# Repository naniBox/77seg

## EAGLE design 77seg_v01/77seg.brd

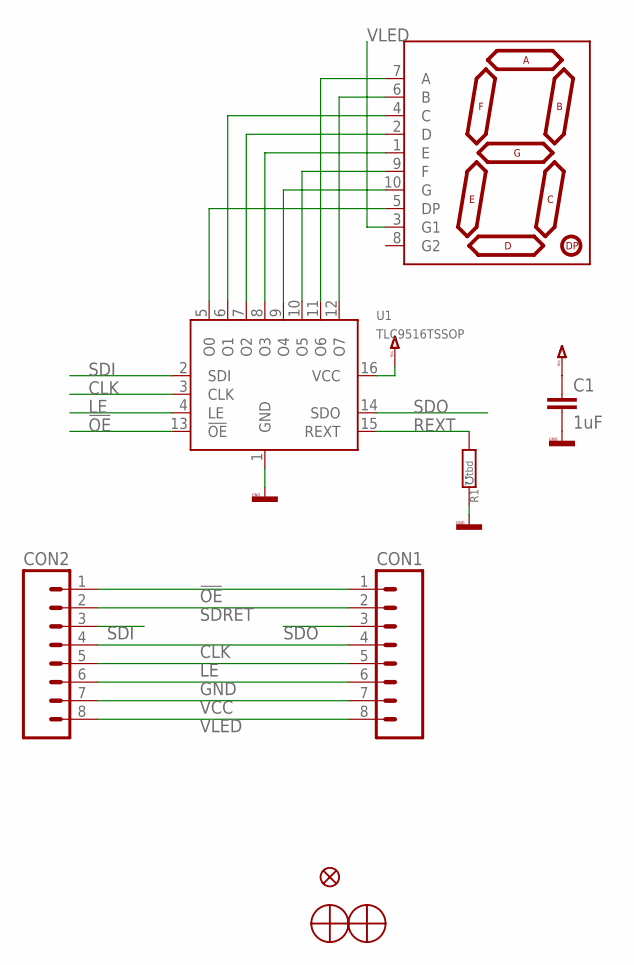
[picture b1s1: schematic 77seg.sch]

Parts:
C1: 1uF; C0603
CON1, CON2: M081.27MM_NO1; 1X08_1.27MM_NO1
JP1: FIDUCIAL1X1.5; FIDUCIAL_1X1.5
R1: tbd; R0603
U1: TLC9516TSSOP; TSSOP16
U$1: 7-SEGMENT-DISPLAYPTH; 7-SEGMENT-DISPLAY
U$2, U$3: SCREW_NOGND; SCREW_M2_NOVIAS

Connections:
!OE: CON1.1, CON2.1, U1.13 (!OE)
CLK: CON1.4, CON2.4, U1.3 (CLK)
GND: C1.2, CON1.6, CON2.6, R1.2, U1.1 (GND)
LE: CON1.5, CON2.5, U1.4 (LE)
unnamed: U1.10 (O5), U$1.9 (F)
unnamed: U1.9 (O4), U$1.10 (G)
unnamed: U1.11 (O6), U$1.7 (A)
unnamed: U1.12 (O7), U$1.6 (B)
unnamed: U1.6 (O1), U$1.4 (C)
unnamed: U1.7 (O2), U$1.2 (D)
unnamed: U1.8 (O3), U$1.1 (E)
unnamed: U1.5 (O0), U$1.5 (DP)
REXT: R1.1, U1.15 (REXT)
SDI: CON2.3, U1.2 (SDI)
SDO: CON1.3, U1.14 (SDO)
SDRET: CON1.2, CON2.2
VCC: C1.1, CON1.7, CON2.7, U1.16 (VCC)
VLED: CON1.8, CON2.8, U$1.3 (G1)

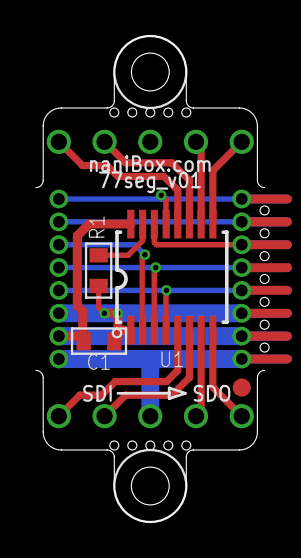
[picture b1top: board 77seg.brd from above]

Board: 2 copper layers, 12.7 x 27.0 mm, 9 parts (1 on the bottom side), 18 nets.

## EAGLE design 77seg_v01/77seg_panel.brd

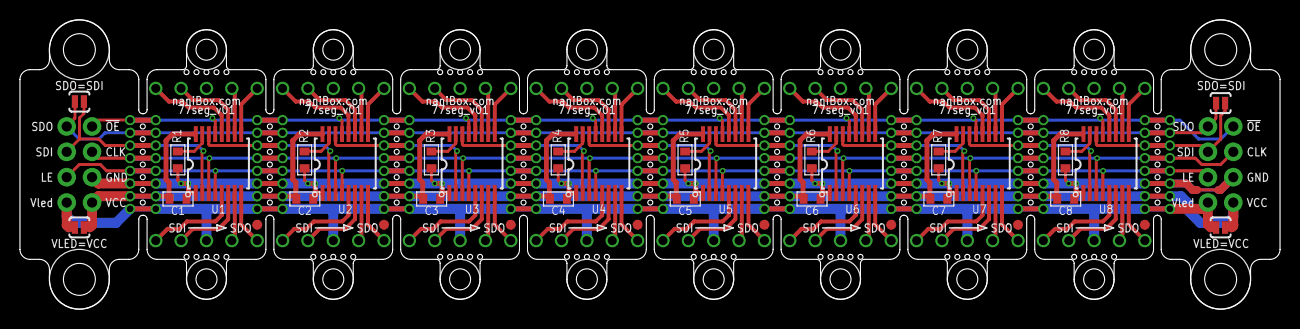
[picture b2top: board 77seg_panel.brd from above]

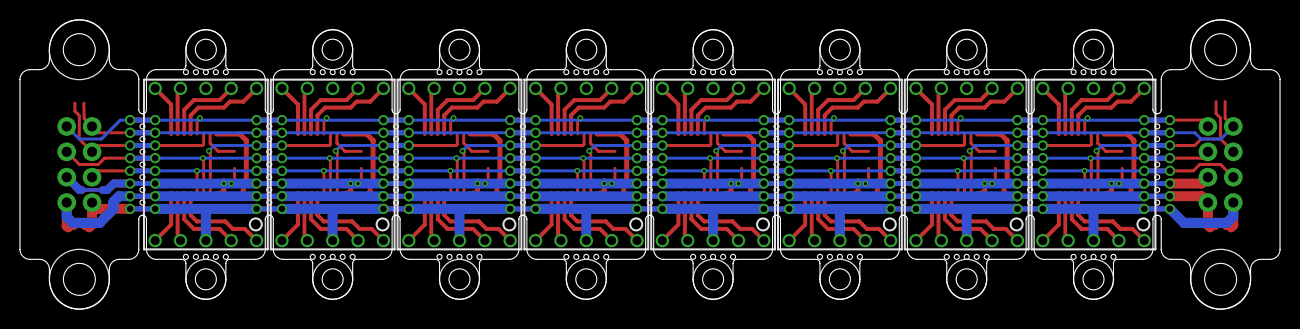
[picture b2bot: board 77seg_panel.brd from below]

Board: 2 copper layers, 126.2 x 29.0 mm, 86 parts (8 on the bottom side), 152 nets.

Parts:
C1, C2, C3, C4, C5, C6, C7, C8: 1uF; C0603
CON1, CON2, CON7, CON8, CON9, CON10, CON11, CON12, CON13, CON14, CON15, CON16, CON17, CON18, CON19, CON20, CON21, CON22: 1X08_1.27MM_NO1
CON3, CON4, CON5, CON6: M04NO1; 1X04_NO1
JP1, JP2, JP3, JP4, JP5, JP6, JP7, JP8: FIDUCIAL1X1.5; FIDUCIAL_1X1.5
R1, R2, R3, R4, R5, R6, R7, R8: tbd; R0603
SDI=SDO1: SJ_2S-NO
SDO=SDI: SJ_2S-NO
U1, U2, U3, U4, U5, U6, U7, U8: TLC9516TSSOP; TSSOP16
U$1, U$2, U$3, U$4: SCREW_NOGNDM3_REDUCED; SCREW_M3_REDUCED
U$5, U$8, U$11, U$14, U$17, U$20, U$23, U$26: 7-SEGMENT-DISPLAYPTH; 7-SEGMENT-DISPLAY
U$6, U$7, U$9, U$10, U$12, U$13, U$15, U$16, U$18, U$19, U$21, U$22, U$24, U$25, U$27, U$28: SCREW_NOGND; SCREW_M2_NOVIAS
VLED=VCC, VLED=VCC1: SJ_2S-NO

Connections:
!OE: CON1.1, CON2.1, CON3.1, CON5.1
!OE1: CON7.1, CON8.1, U1.13
!OE2: CON9.1, CON10.1, U2.13
!OE3: CON11.1, CON12.1, U3.13
!OE4: CON13.1, CON14.1, U4.13
!OE5: CON15.1, CON16.1, U5.13
!OE6: CON17.1, CON18.1, U6.13
!OE7: CON19.1, CON20.1, U7.13
!OE8: CON21.1, CON22.1, U8.13
CLK: CON1.4, CON2.4, CON3.2, CON5.2
CLK1: CON7.4, CON8.4, U1.3
CLK2: CON9.4, CON10.4, U2.3
CLK3: CON11.4, CON12.4, U3.3
CLK4: CON13.4, CON14.4, U4.3
CLK5: CON15.4, CON16.4, U5.3
CLK6: CON17.4, CON18.4, U6.3
CLK7: CON19.4, CON20.4, U7.3
CLK8: CON21.4, CON22.4, U8.3
GND: CON1.6, CON2.6, CON3.3, CON5.3
GND1: C1.2, CON7.6, CON8.6, R1.2, U1.1
GND2: C2.2, CON9.6, CON10.6, R2.2, U2.1
GND3: C3.2, CON11.6, CON12.6, R3.2, U3.1
GND4: C4.2, CON13.6, CON14.6, R4.2, U4.1
GND5: C5.2, CON15.6, CON16.6, R5.2, U5.1
GND6: C6.2, CON17.6, CON18.6, R6.2, U6.1
GND7: C7.2, CON19.6, CON20.6, R7.2, U7.1
GND8: C8.2, CON21.6, CON22.6, R8.2, U8.1
LE: CON1.5, CON2.5, CON4.3, CON6.3
LE1: CON7.5, CON8.5, U1.4
LE2: CON9.5, CON10.5, U2.4
LE3: CON11.5, CON12.5, U3.4
LE4: CON13.5, CON14.5, U4.4
LE5: CON15.5, CON16.5, U5.4
LE6: CON17.5, CON18.5, U6.4
LE7: CON19.5, CON20.5, U7.4
LE8: CON21.5, CON22.5, U8.4
unnamed: U2.10, U$8.9
unnamed: U2.9, U$8.10
unnamed: U1.10, U$5.9
unnamed: U1.9, U$5.10
unnamed: U2.11, U$8.7
unnamed: U2.12, U$8.6
unnamed: U2.6, U$8.4
unnamed: U2.7, U$8.2
unnamed: U2.8, U$8.1
unnamed: U1.11, U$5.7
unnamed: U1.12, U$5.6
unnamed: U1.6, U$5.4
unnamed: U1.7, U$5.2
unnamed: U1.8, U$5.1
unnamed: U2.5, U$8.5
unnamed: U3.10, U$11.9
unnamed: U1.5, U$5.5
unnamed: U3.9, U$11.10
unnamed: U3.11, U$11.7
unnamed: U3.12, U$11.6
unnamed: U3.6, U$11.4
unnamed: U3.7, U$11.2
unnamed: U3.8, U$11.1
unnamed: U3.5, U$11.5
unnamed: U4.10, U$14.9
unnamed: U4.9, U$14.10
unnamed: U4.11, U$14.7
unnamed: U4.12, U$14.6
unnamed: U4.6, U$14.4
unnamed: U4.7, U$14.2
unnamed: U4.8, U$14.1
unnamed: U4.5, U$14.5
unnamed: U5.10, U$17.9
unnamed: U5.9, U$17.10
unnamed: U5.11, U$17.7
unnamed: U5.12, U$17.6
unnamed: U5.6, U$17.4
unnamed: U5.7, U$17.2
unnamed: U5.8, U$17.1
unnamed: U5.5, U$17.5
unnamed: U6.10, U$20.9
unnamed: U6.9, U$20.10
unnamed: U6.11, U$20.7
unnamed: U6.12, U$20.6
unnamed: U6.6, U$20.4
unnamed: U6.7, U$20.2
unnamed: U6.8, U$20.1
unnamed: U6.5, U$20.5
unnamed: U7.10, U$23.9
unnamed: U7.9, U$23.10
unnamed: U7.11, U$23.7
unnamed: U7.12, U$23.6
unnamed: U7.6, U$23.4
unnamed: U7.7, U$23.2
unnamed: U7.8, U$23.1
unnamed: U7.5, U$23.5
unnamed: U8.10, U$26.9
unnamed: U8.9, U$26.10
unnamed: U8.11, U$26.7
unnamed: U8.12, U$26.6
unnamed: U8.6, U$26.4
unnamed: U8.7, U$26.2
unnamed: U8.8, U$26.1
unnamed: U8.5, U$26.5
REXT: R1.1, U1.15
REXT1: R2.1, U2.15
REXT2: R3.1, U3.15
REXT3: R4.1, U4.15
REXT4: R5.1, U5.15
REXT5: R6.1, U6.15
REXT6: R7.1, U7.15
REXT7: R8.1, U8.15
SDI: CON1.3, CON2.3, CON4.2, CON6.2, SDI=SDO1.1, SDO=SDI.1
SDI1: CON8.3, U1.2
SDI2: CON10.3, U2.2
SDI3: CON12.3, U3.2
SDI4: CON14.3, U4.2
SDI5: CON16.3, U5.2
SDI6: CON18.3, U6.2
SDI7: CON20.3, U7.2
SDI8: CON22.3, U8.2
SDO: CON1.2, CON2.2, CON4.1, CON6.1, SDI=SDO1.2, SDO=SDI.2
SDO1: CON7.3, U1.14
SDO2: CON9.3, U2.14
SDO3: CON11.3, U3.14
SDO4: CON13.3, U4.14
SDO5: CON15.3, U5.14
SDO6: CON17.3, U6.14
SDO7: CON19.3, U7.14
SDO8: CON21.3, U8.14
SDRET: CON7.2, CON8.2
SDRET1: CON9.2, CON10.2
SDRET2: CON11.2, CON12.2
SDRET3: CON13.2, CON14.2
SDRET4: CON15.2, CON16.2
SDRET5: CON17.2, CON18.2
SDRET6: CON19.2, CON20.2
SDRET7: CON21.2, CON22.2
VCC: CON1.7, CON2.7, CON3.4, CON5.4, VLED=VCC.1, VLED=VCC1.1
VCC1: C1.1, CON7.7, CON8.7, U1.16
VCC2: C2.1, CON9.7, CON10.7, U2.16
VCC3: C3.1, CON11.7, CON12.7, U3.16
VCC4: C4.1, CON13.7, CON14.7, U4.16
VCC5: C5.1, CON15.7, CON16.7, U5.16
VCC6: C6.1, CON17.7, CON18.7, U6.16
VCC7: C7.1, CON19.7, CON20.7, U7.16
VCC8: C8.1, CON21.7, CON22.7, U8.16
VLED: CON1.8, CON2.8, CON4.4, CON6.4, VLED=VCC.2, VLED=VCC1.2
VLED1: CON7.8, CON8.8, U$5.3
VLED2: CON9.8, CON10.8, U$8.3
VLED3: CON11.8, CON12.8, U$11.3
VLED4: CON13.8, CON14.8, U$14.3
VLED5: CON15.8, CON16.8, U$17.3
VLED6: CON17.8, CON18.8, U$20.3
VLED7: CON19.8, CON20.8, U$23.3
VLED8: CON21.8, CON22.8, U$26.3

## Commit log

2013-08-27 Added first revision of the 77seg driver...
2013-08-27 Just moved ends around.
2013-08-27 Fix some layer crappiness!

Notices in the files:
parts and their libraries:
SparkFun: Licensing: CC v3.0 Share-Alike You are welcome to use this library for commercial purposes.
